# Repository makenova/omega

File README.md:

# Omega

Hot swap

Solder

Omega4

The omega is a hot swap 30%(30 or 29 keys depending on the layout you choose) inspired by the [Zlant](https://www.reddit.com/r/MechanicalKeyboards/search?q=zlant&restrict_sr=1) and the [Alpha 28](https://geekhack.org/index.php?topic=99040.0) keyboards.  
The omeaga4 adds a breakaway 4th row with a few options to make this more than a novelty piece.

The plate files, stls for 3D printing, and STEP files can be found in the [docs](./docs) folder.  
There are also gerbers already generated in the gerber folders.

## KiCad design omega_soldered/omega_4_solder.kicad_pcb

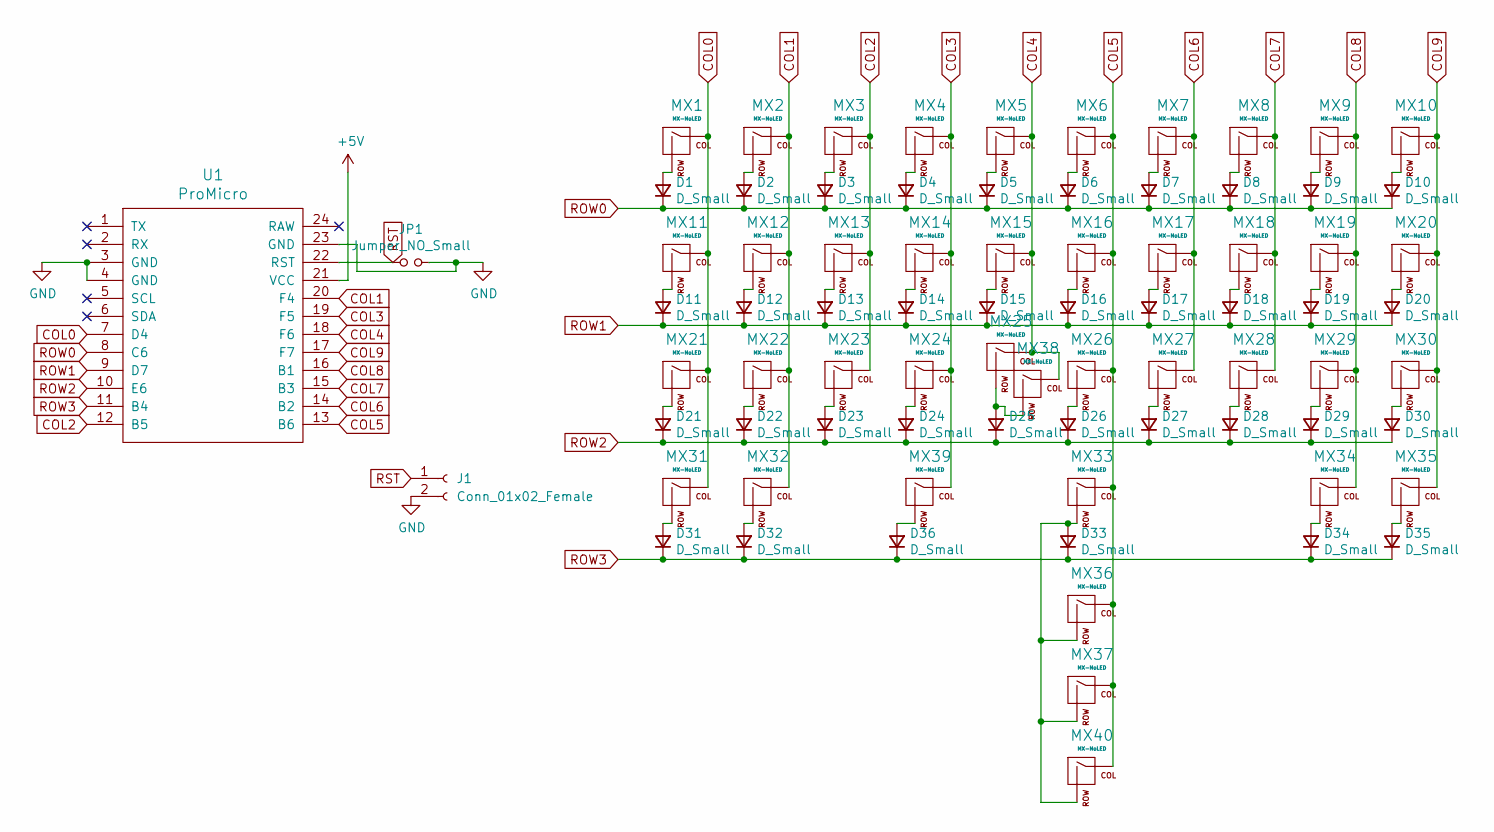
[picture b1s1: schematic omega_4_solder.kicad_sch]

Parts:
D1, D2, D3, D4, D5, D6, D7, D8, D9, D10, D11, D12, D13, D14, D15, D16, D17, D18, D19, D20, D21, D22, D23, D24, D25, D26, D27, D28, D29, D30, D31, D32, D33, D34, D35, D36: D_Small; Diode-Hybrid-Back
J1: Conn_01x02_Female; PinHeader_1x02_P2.00mm_Vertical
JP1: Jumper_NO_Small; Jumper-UserFriendly-Small
MX1, MX2, MX3, MX4, MX5, MX6, MX7, MX8, MX9, MX10, MX11, MX12, MX13, MX14, MX15, MX16, MX17, MX18, MX19, MX20, MX21, MX22, MX23, MX24, MX25, MX26, MX27, MX28, MX29, MX30, MX31, MX32, MX34, MX35: MX-NoLED; MXOnly-1U-NoLED
MX33: MX-NoLED; MX-10U-ReversedStabilizers-NoLED
MX36: MX-NoLED; MXOnly-6U-ReversedStabilizers-NoLED
MX37: MX-NoLED; MXOnly-6U-Centered-NoLED
MX38: MX-NoLED; MXOnly-2U-ReversedStabilizers-NoLED
MX39, MX40: MX-NoLED; MXOnly-3U-ReversedStabilizers-NoLED
U1: ProMicro

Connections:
+5V: U1.21 (VCC)
COL0: MX1.1 (COL), MX11.1 (COL), MX21.1 (COL), MX31.1 (COL), U1.7 (D4)
COL1: MX2.1 (COL), MX12.1 (COL), MX22.1 (COL), MX32.1 (COL), U1.20 (F4)
COL2: MX3.1 (COL), MX13.1 (COL), MX23.1 (COL), U1.12 (B5)
COL3: MX4.1 (COL), MX14.1 (COL), MX24.1 (COL), MX39.1 (COL), U1.19 (F5)
COL4: MX5.1 (COL), MX15.1 (COL), MX25.1 (COL), MX38.1 (COL), U1.18 (F6)
COL5: MX6.1 (COL), MX16.1 (COL), MX26.1 (COL), MX33.1 (COL), MX36.1 (COL), MX37.1 (COL), MX40.1 (COL), U1.13 (B6)
COL6: MX7.1 (COL), MX17.1 (COL), MX27.1 (COL), U1.14 (B2)
COL7: MX8.1 (COL), MX18.1 (COL), MX28.1 (COL), U1.15 (B3)
COL8: MX9.1 (COL), MX19.1 (COL), MX29.1 (COL), MX34.1 (COL), U1.16 (B1)
COL9: MX10.1 (COL), MX20.1 (COL), MX30.1 (COL), MX35.1 (COL), U1.17 (F7)
GND: J1.2, JP1.2, U1.3 (GND), U1.4 (GND), U1.23 (GND)
unnamed: D1.2 (A), MX1.2 (ROW)
unnamed: D2.2 (A), MX2.2 (ROW)
unnamed: D3.2 (A), MX3.2 (ROW)
unnamed: D4.2 (A), MX4.2 (ROW)
unnamed: D5.2 (A), MX5.2 (ROW)
unnamed: D6.2 (A), MX6.2 (ROW)
unnamed: D7.2 (A), MX7.2 (ROW)
unnamed: D8.2 (A), MX8.2 (ROW)
unnamed: D9.2 (A), MX9.2 (ROW)
unnamed: D10.2 (A), MX10.2 (ROW)
unnamed: D11.2 (A), MX11.2 (ROW)
unnamed: D12.2 (A), MX12.2 (ROW)
unnamed: D13.2 (A), MX13.2 (ROW)
unnamed: D14.2 (A), MX14.2 (ROW)
unnamed: D15.2 (A), MX15.2 (ROW)
unnamed: D16.2 (A), MX16.2 (ROW)
unnamed: D17.2 (A), MX17.2 (ROW)
unnamed: D18.2 (A), MX18.2 (ROW)
unnamed: D19.2 (A), MX19.2 (ROW)
unnamed: D20.2 (A), MX20.2 (ROW)
unnamed: D21.2 (A), MX21.2 (ROW)
unnamed: D22.2 (A), MX22.2 (ROW)
unnamed: D23.2 (A), MX23.2 (ROW)
unnamed: D24.2 (A), MX24.2 (ROW)
unnamed: D25.2 (A), MX25.2 (ROW), MX38.2 (ROW)
unnamed: D26.2 (A), MX26.2 (ROW)
unnamed: D27.2 (A), MX27.2 (ROW)
unnamed: D28.2 (A), MX28.2 (ROW)
unnamed: D29.2 (A), MX29.2 (ROW)
unnamed: D30.2 (A), MX30.2 (ROW)
unnamed: D31.2 (A), MX31.2 (ROW)
unnamed: D32.2 (A), MX32.2 (ROW)
unnamed: D33.2 (A), MX33.2 (ROW), MX36.2 (ROW), MX37.2 (ROW), MX40.2 (ROW)
unnamed: D34.2 (A), MX34.2 (ROW)
unnamed: D35.2 (A), MX35.2 (ROW)
unnamed: D36.2 (A), MX39.2 (ROW)
ROW0: D1.1 (K), D2.1 (K), D3.1 (K), D4.1 (K), D5.1 (K), D6.1 (K), D7.1 (K), D8.1 (K), D9.1 (K), D10.1 (K), U1.8 (C6)
ROW1: D11.1 (K), D12.1 (K), D13.1 (K), D14.1 (K), D15.1 (K), D16.1 (K), D17.1 (K), D18.1 (K), D19.1 (K), D20.1 (K), U1.9 (D7)
ROW2: D21.1 (K), D22.1 (K), D23.1 (K), D24.1 (K), D25.1 (K), D26.1 (K), D27.1 (K), D28.1 (K), D29.1 (K), D30.1 (K), U1.10 (E6)
ROW3: D31.1 (K), D32.1 (K), D33.1 (K), D34.1 (K), D35.1 (K), D36.1 (K), U1.11 (B4)
RST: J1.1, JP1.1, U1.22 (RST)

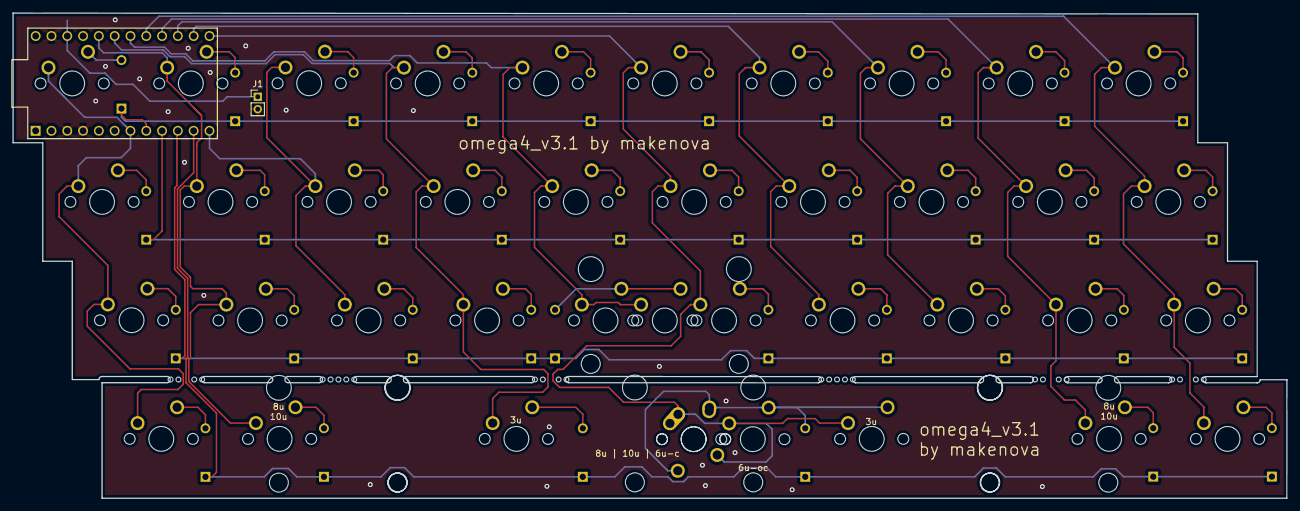
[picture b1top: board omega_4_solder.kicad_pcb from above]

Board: 2 copper layers, 204.8 x 78.0 mm, 79 parts (1 on the bottom side), 52 nets.

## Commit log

2020-06-01 make it so
    add libraries
    set up schematic
    layout pcb components
    begin routing
2020-06-01 add readme
2020-06-01 generate gerber for tracespace
2020-06-08 flip pro micor and generate assembly files
2020-06-16 separate hot swap and soldered version
2020-06-19 add solder version
2020-06-19 update docs and plate
2020-07-21 work
2020-07-21 messing with submodules
2020-07-25 more messing with submodules
2020-08-13 add: omega_4
2020-08-17 generate production files
2020-08-17 add jumper to skeleton case
    jumper get the solder mask to show up
2020-08-18 update skeleton top plate
    remove acoustic cuts and round off 90 degree angles
2020-08-20 update skeleton case to allow 3mm between cuts and regen prod files
2020-11-03 update spacebars on omega4
    fix spacebar positioning on omega4
2020-11-03 update omega4 case files
    move stabilizer cutouts
2020-11-04 update soldered omega
    flip pro micro footprint
    shuffle mounting holes
    make stl files to 3D print for testing
    regenerate gerbers
2020-11-05 update soldered omega
    increase stanoff hole size through the pcb
    update stl files and step files
    shuffle file locations
    regenerate gerbers
2020-11-13 do not use series pins on omega soldered
    regenerage gerber files for omega soldered and omega 4
2022-03-12 wip: v3
    break away bottom row
2022-03-12 update mouse bites
2022-08-09 add split spacebar to breakaway row
2022-08-09 update readme images
